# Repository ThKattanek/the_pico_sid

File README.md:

# ThePicoSID
This is a MOS-6581 / MOS-8580 replacement on the base from reSID on the raspberry pi pico or rp2040.
The first pcb prototype, for stable testings.

#### Here are a few videos of me in german language.

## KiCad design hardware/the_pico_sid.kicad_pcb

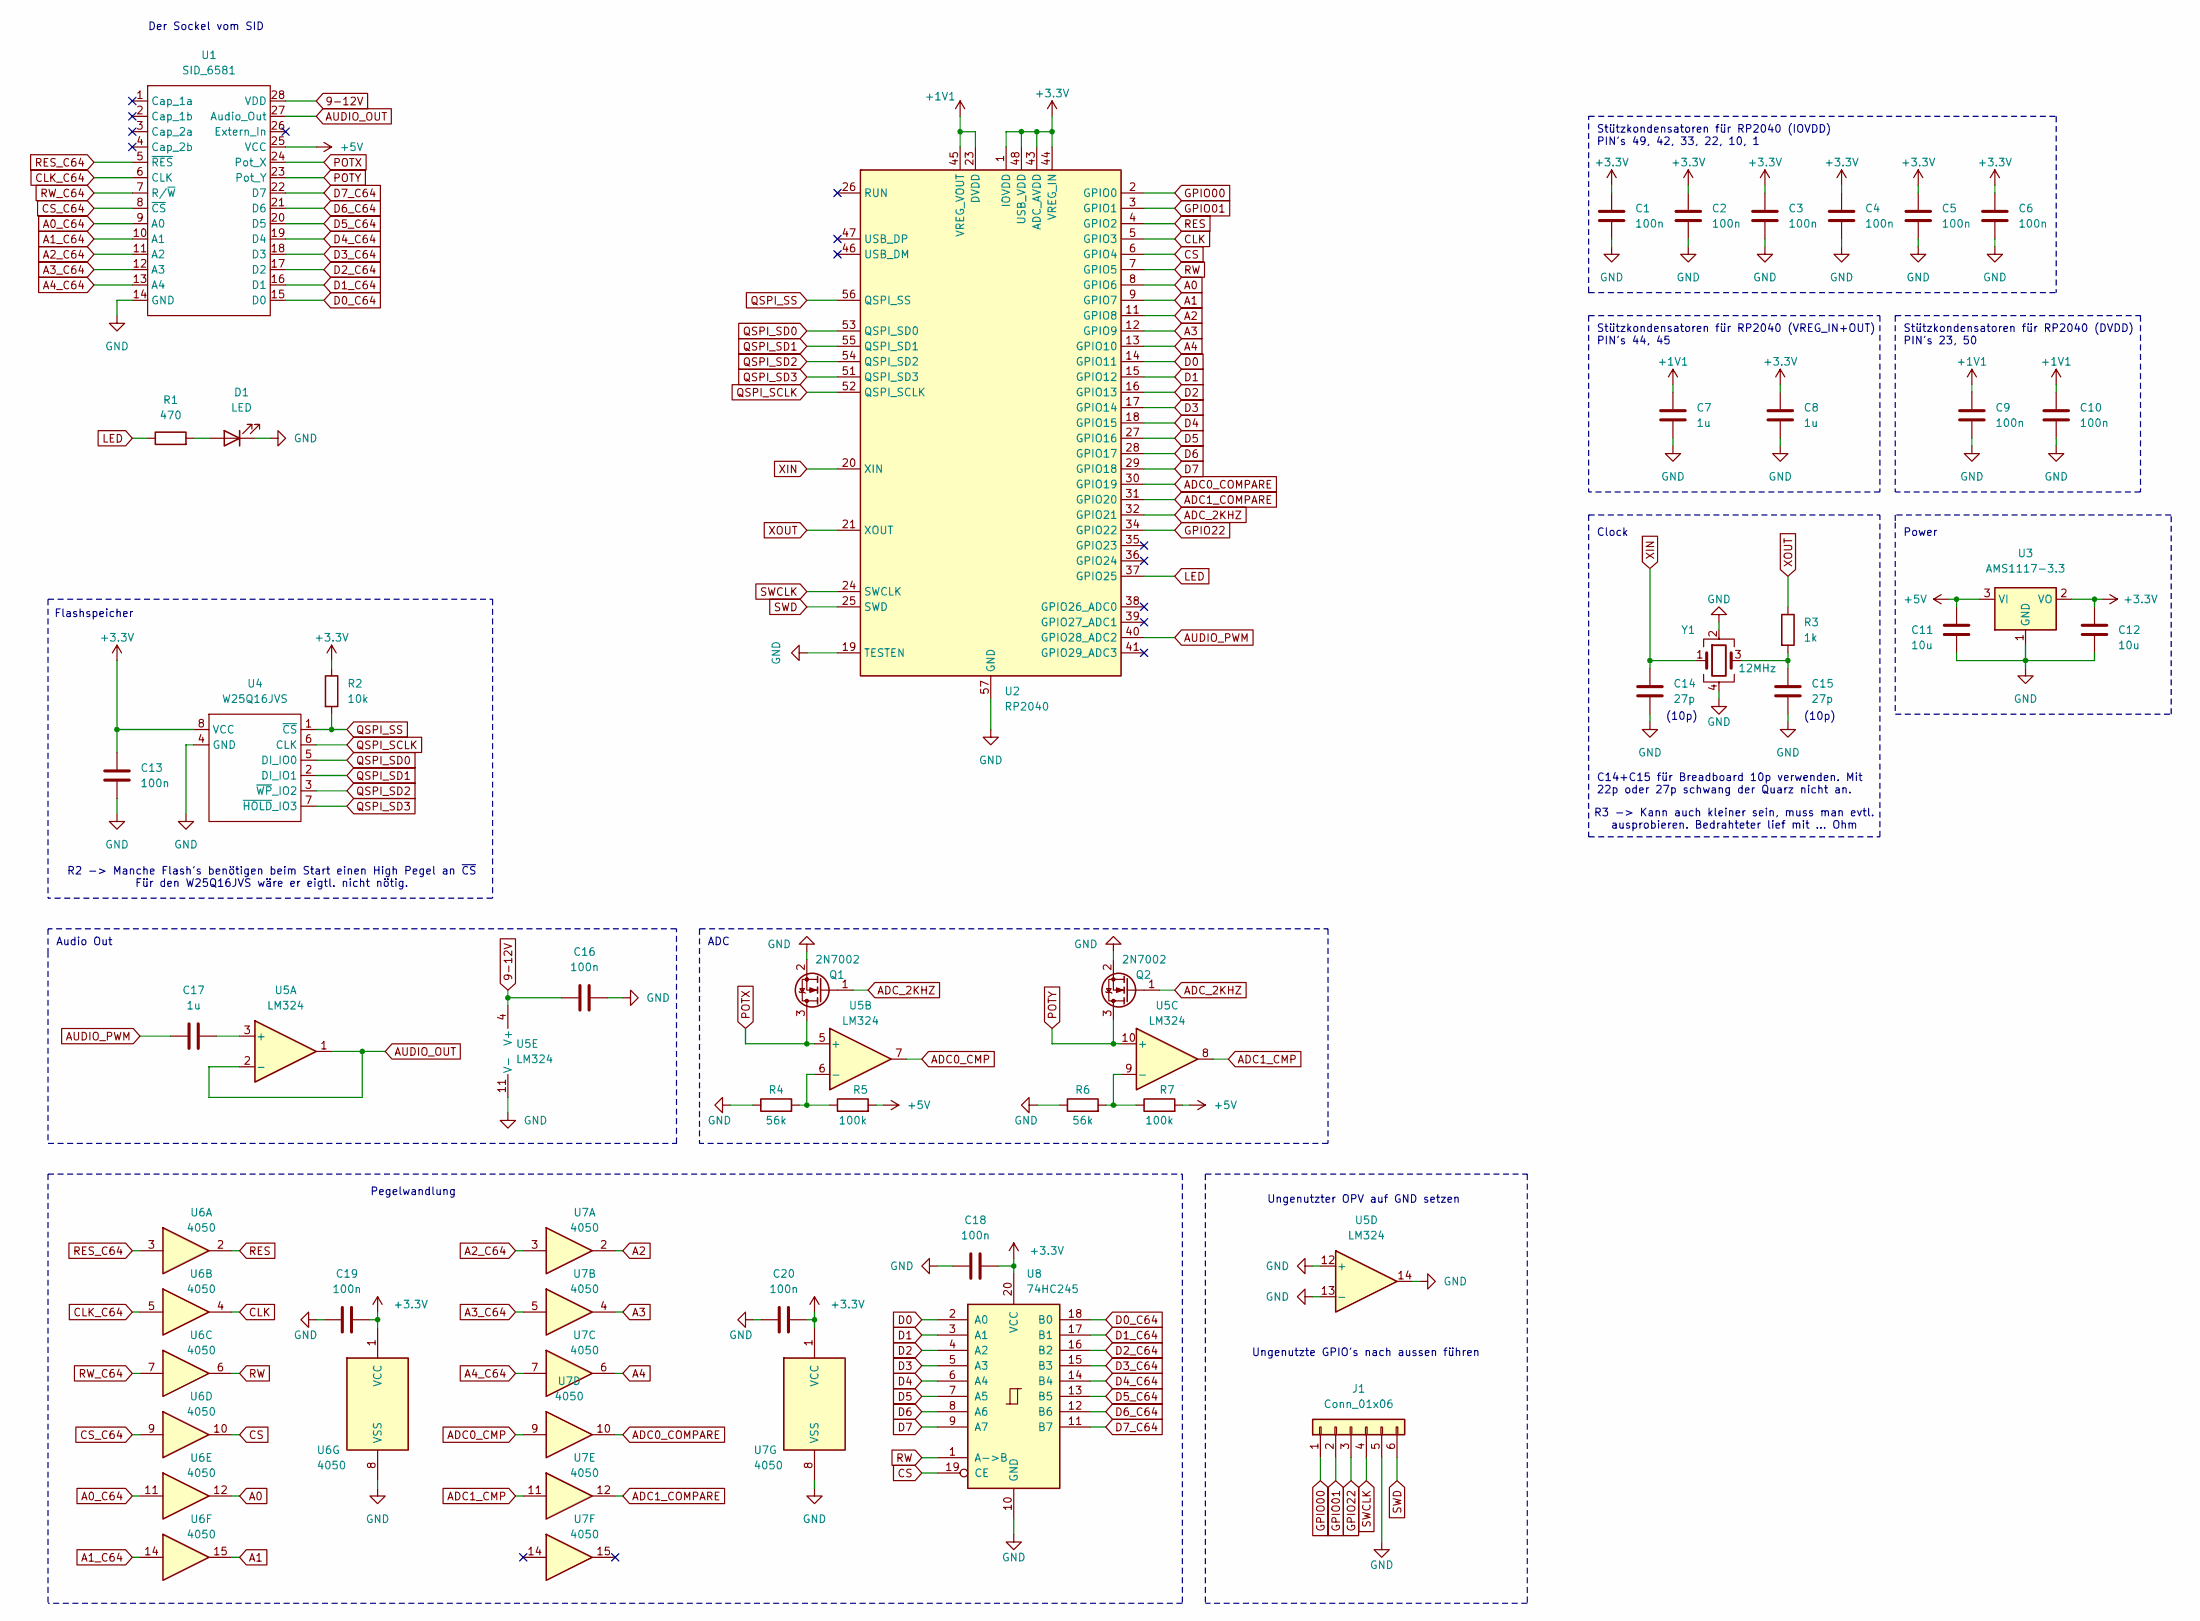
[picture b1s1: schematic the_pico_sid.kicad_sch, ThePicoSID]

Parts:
C1, C2, C3, C4, C5, C6, C9, C10, C13, C16, C18, C19, C20: 100n; C_0603_1608Metric
C7, C8, C17: 1u; C_0603_1608Metric
C11, C12: 10u; C_0603_1608Metric
C14, C15: 27p; C_0603_1608Metric
D1: LED; LED_0805_2012Metric
J1: Conn_01x06; PinSocket_1x06_P1.27mm_Vertical
Q1, Q2: 2N7002; SOT-23
R1: 470; R_0603_1608Metric
R2: 10k; R_0603_1608Metric
R3: 1k; R_0603_1608Metric
R4, R6: 56k; R_0603_1608Metric
R5, R7: 100k; R_0603_1608Metric
U1: SID_6581; c64_sid_pins
U2: RP2040; QFN-56-1EP_7x7mm_P0.4mm_EP3.2x3.2mm
U3: AMS1117-3.3; SOT-223-3_TabPin2
U4: W25Q16JVS; SO-8_5.3x6.2mm_P1.27mm
U5: LM324; SOIC-14_3.9x8.7mm_P1.27mm
U6, U7: 4050; SOIC-16_3.9x9.9mm_P1.27mm
U8: 74HC245; SOIC-20W_7.5x12.8mm_P1.27mm
Y1: 12MHz; Crystal_SMD_EuroQuartz_MJ-4Pin_5.0x3.2mm

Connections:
9-12V: C16.1, U1.28 (VDD), U5.4 (V+)
+1V1: C7.1, C9.1, C10.1, U2.23 (DVDD), U2.45 (VREG_VOUT), U2.50 (DVDD)
+3.3V: C1.1, C2.1, C3.1, C4.1, C5.1, C6.1, C8.1, C12.1, C13.1, C18.2, C19.2, C20.2, R2.1, U2.1 (IOVDD), U2.10 (IOVDD), U2.22 (IOVDD), U2.33 (IOVDD), U2.42 (IOVDD), U2.43 (ADC_AVDD), U2.44 (VREG_IN), U2.48 (USB_VDD), U2.49 (IOVDD), U3.2 (VO), U4.8 (VCC), U6.1 (VCC), U7.1 (VCC), U8.20 (VCC)
+5V: C11.1, R5.2, R7.2, U1.25 (VCC), U3.3 (VI)
A0: U2.8 (GPIO6), U6.12
A0_C64: U1.9 (A0), U6.11
A1: U2.9 (GPIO7), U6.15
A1_C64: U1.10 (A1), U6.14
A2: U2.11 (GPIO8), U7.2
A2_C64: U1.11 (A2), U7.3
A3: U2.12 (GPIO9), U7.4
A3_C64: U1.12 (A3), U7.5
A4: U2.13 (GPIO10), U7.6
A4_C64: U1.13 (A4), U7.7
ADC0_CMP: U5.7, U7.9
ADC0_COMPARE: U2.30 (GPIO19), U7.10
ADC1_CMP: U5.8, U7.11
ADC1_COMPARE: U2.31 (GPIO20), U7.12
ADC_2KHZ: Q1.1 (G), Q2.1 (G), U2.32 (GPIO21)
AUDIO_OUT: U1.27 (Audio_Out), U5.1, U5.2 (-)
AUDIO_PWM: C17.1, U2.40 (GPIO28_ADC2)
CLK: U2.5 (GPIO3), U6.4
CLK_C64: U1.6 (CLK), U6.5
CS: U2.6 (GPIO4), U6.10, U8.19 (CE)
CS_C64: U1.8 (~CS), U6.9
D0: U2.14 (GPIO11), U8.2 (A0)
D0_C64: U1.15 (D0), U8.18 (B0)
D1: U2.15 (GPIO12), U8.3 (A1)
D1_C64: U1.16 (D1), U8.17 (B1)
D2: U2.16 (GPIO13), U8.4 (A2)
D2_C64: U1.17 (D2), U8.16 (B2)
D3: U2.17 (GPIO14), U8.5 (A3)
D3_C64: U1.18 (D3), U8.15 (B3)
D4: U2.18 (GPIO15), U8.6 (A4)
D4_C64: U1.19 (D4), U8.14 (B4)
D5: U2.27 (GPIO16), U8.7 (A5)
D5_C64: U1.20 (D5), U8.13 (B5)
D6: U2.28 (GPIO17), U8.8 (A6)
D6_C64: U1.21 (D6), U8.12 (B6)
D7: U2.29 (GPIO18), U8.9 (A7)
D7_C64: U1.22 (D7), U8.11 (B7)
GND: C1.2, C2.2, C3.2, C4.2, C5.2, C6.2, C7.2, C8.2, C9.2, C10.2, C11.2, C12.2, C13.2, C14.2, C15.2, C16.2, C18.1, C19.1, C20.1, D1.1 (K), J1.5, Q1.2 (S), Q2.2 (S), R4.1, R6.1, U1.14 (GND), U2.19 (TESTEN), U2.57 (GND), U3.1 (GND), U4.4 (GND), U5.11 (V-), U5.12 (+), U5.13 (-), U5.14, U6.8 (VSS), U7.8 (VSS), U8.10 (GND), Y1.2, Y1.4
GPIO00: J1.1, U2.2 (GPIO0)
GPIO01: J1.2, U2.3 (GPIO1)
GPIO22: J1.3, U2.34 (GPIO22)
LED: R1.1, U2.37 (GPIO25)
unnamed: C15.1, R3.2, Y1.3
unnamed: D1.2 (A), R1.2
unnamed: C17.2, U5.3 (+)
unnamed: R4.2, R5.1, U5.6 (-)
unnamed: R6.2, R7.1, U5.9 (-)
POTX: Q1.3 (D), U1.24 (Pot_X), U5.5 (+)
POTY: Q2.3 (D), U1.23 (Pot_Y), U5.10 (+)
QSPI_SCLK: U2.52 (QSPI_SCLK), U4.6 (CLK)
QSPI_SD0: U2.53 (QSPI_SD0), U4.5 (DI_IO0)
QSPI_SD1: U2.55 (QSPI_SD1), U4.2 (DI_IO1)
QSPI_SD2: U2.54 (QSPI_SD2), U4.3 (~WP_IO2)
QSPI_SD3: U2.51 (QSPI_SD3), U4.7 (~HOLD_IO3)
QSPI_SS: R2.2, U2.56 (QSPI_SS), U4.1 (~CS)
RES: U2.4 (GPIO2), U6.2
RES_C64: U1.5 (~RES), U6.3
RW: U2.7 (GPIO5), U6.6, U8.1 (A->B)
RW_C64: U1.7 (R/~W), U6.7
SWCLK: J1.4, U2.24 (SWCLK)
SWD: J1.6, U2.25 (SWD)
XIN: C14.1, U2.20 (XIN), Y1.1
XOUT: R3.1, U2.21 (XOUT)

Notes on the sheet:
Ungenutzter OPV auf GND setzen
Stützkondensatoren für RP2040 (DVDD) PIN's 23, 50
(10p)
Der Sockel vom SID
Clock
Audio Out
Power
Stützkondensatoren für RP2040 (VREG_IN+OUT) PIN's 44, 45
Flashspeicher
R3 -> Kann auch kleiner sein, muss man evtl. ausprobieren. Bedrahteter lief mit ... Ohm
R2 -> Manche Flash's benötigen beim Start einen High Pegel an ~{CS} Für den W25Q16JVS wäre er eigtl. nicht nötig.
Pegelwandlung
Stützkondensatoren für RP2040 (IOVDD) PIN's 49, 42, 33, 22, 10, 1
C14+C15 für Breadboard 10p verwenden. Mit 22p oder 27p schwang der Quarz nicht an.
Ungenutzte GPIO's nach aussen führen
ADC

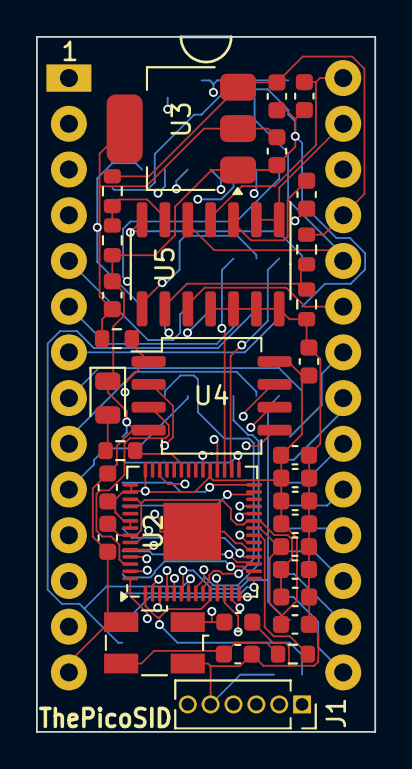
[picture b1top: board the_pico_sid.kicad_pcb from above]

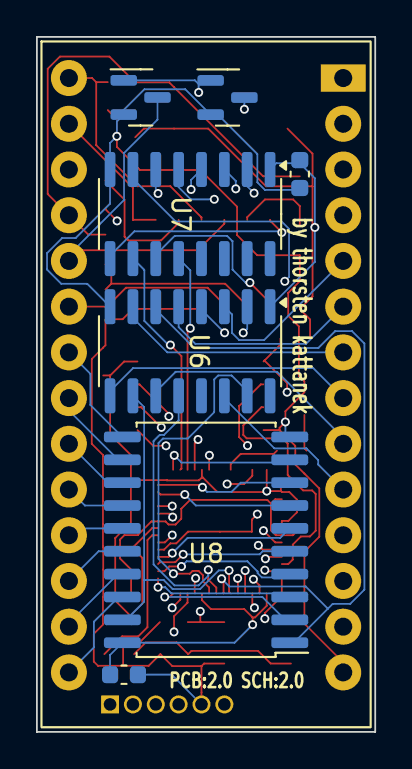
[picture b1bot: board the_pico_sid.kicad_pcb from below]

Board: 4 copper layers, 18.8 x 38.6 mm, 40 parts (8 on the bottom side), 67 nets.

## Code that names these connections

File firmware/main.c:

//////////////////////////////////////////////////
//                                              //
// ThePicoSID                                   //
// von Thorsten Kattanek                        //
//                                              //
// #file: main.c                                //
//                                              //
// https://github.com/ThKattanek/the_pico_sid   //
//                                              //
//////////////////////////////////////////////////

#include <stdio.h>
#include <pico/multicore.h>
#include <hardware/pio.h>
#include <hardware/dma.h>
#include <hardware/pwm.h>
#include <hardware/adc.h>

#include "write_sid_reg.pio.h"
#include "read_sid_reg.pio.h"
#include "dma_read.pio.h"

#include "sid.h"

#include "version.h"

// PIN MAPPING
#define RES_PIN 2
#define CLK_PIN 3		// Atention: When change this gpio, then also change this in write_sid_reg.pio
#define CS_PIN 4
#define RW_PIN 5
#define ADRR_PIN 6
#define DATA_PIN 11
#define AUDIO_PIN 28
#define ADC0_COMPARE_PIN 19
#define ADC1_COMPARE_PIN 20
#define ADC_2KHz_PIN 21

#define PICO_LED_PIN 25

#define ADC_OFFSET -5



volatile bool reset_state = true;

volatile PIO pio;
volatile uint sm0;	// write sid
volatile uint sm1;	// read sid
volatile uint sm2;	// dma read

volatile uint slice_num;

void InitPWMAudio(uint audio_out_gpio);
void DmaReadInit(PIO pio, uint sm, uint8_t* base_address);

void C64Reset(uint gpio, uint32_t events) 
{
    if (events & GPIO_IRQ_EDGE_FALL) 
	{
		// C64 Reset
		// Normalerweise erst wenn RESET 10 Zyklen auf Lo war
        SidSetAudioOut(false);
		SidReset();
    }
	else if (events & GPIO_IRQ_EDGE_RISE) 
	{
		// C64 Reset Ende
        SidSetAudioOut(true);
    }
}

void WriteSidReg()
{
	if (pio0_hw->irq & 1) 
	{
		pio0_hw->irq = 1;

		uint16_t incomming = pio->rxf[sm0];
		SidWriteReg(incomming >> 2, (incomming >> 7) & 0xff);
	}
}

void Core1Entry() 
{
	InitPWMAudio(AUDIO_PIN);

    while (1)
	{
	}
}

void GetVersionNumber(uint8_t *major, uint8_t *minor, uint8_t *patch)
{
	*major = VERSION_MAJOR;
	*minor = VERSION_MINOR;
	*patch = VERSION_PATCH;
}

int main() {

	//default clock is 125000kHz
	set_sys_clock_khz(248000, true); // Kann Normal bis 133MHz laufen, funktioniert bei mir auch bis 266MHz

	stdio_init_all();	

	// Pico LED
	gpio_init(PICO_LED_PIN);
	gpio_set_dir(PICO_LED_PIN, true);
	gpio_put(PICO_LED_PIN, true);

	// ADC
	gpio_init(ADC_2KHz_PIN);
	gpio_set_dir(ADC_2KHz_PIN, true);	// Output

	gpio_init(ADC0_COMPARE_PIN);
	gpio_init(ADC1_COMPARE_PIN);

	gpio_set_dir(ADC0_COMPARE_PIN, false);	// Input
	gpio_set_dir(ADC1_COMPARE_PIN, false);	// Input

	// Init SID
	// memory for the sid io
    uint8_t* sid_io = memalign(32, 32);
	for(int i=0; i<32; i++)
		sid_io[i] = i;

	SidInit(sid_io);
	SidSetChipTyp(MOS_8580);
	SidEnableFilter(true);
	
	// UART Start Message PicoSID
	printf("ThePicoSID by Thorsten Kattanek\n");

	uint8_t v_major, v_minor, v_patch;
	GetVersionNumber(&v_major, &v_minor, &v_patch);

	printf("Firmware Version: %d.%d.%d\n", v_major, v_minor, v_patch);
	
	// PIO Program initialize
	pio = pio0;

	// PIO Write SID
	uint offset = pio_add_program(pio, &write_sid_reg_program);
	sm0 = pio_claim_unused_sm(pio, true);
	write_sid_reg_program_init(pio, sm0, offset, CLK_PIN, CS_PIN);	//CLK_PIN + RW_PIN + A0-A4 + D0-D7 all PIN Count is 15
	irq_set_exclusive_handler(PIO0_IRQ_0, WriteSidReg);
	irq_set_enabled(PIO0_IRQ_0, true);
	pio0_hw->inte0 = PIO_IRQ0_INTE_SM0_BITS;

	// PIO Read SID
	offset = pio_add_program(pio, &read_sid_reg_program);
	sm1 = pio_claim_unused_sm(pio, true);
	read_sid_reg_program_init(pio, sm1, offset, CLK_PIN, CS_PIN, DATA_PIN);

	// PIO DMA READ
	offset = pio_add_program(pio, &dma_read_program);
	sm2 = pio_claim_unused_sm(pio, true);
	dma_read_program_init(pio, sm2, offset, ADRR_PIN, DATA_PIN, sid_io);
	DmaReadInit(pio, sm2, sid_io);

	// IRQ für die RESET Leitung
	gpio_init(RES_PIN);
    gpio_set_dir(RES_PIN, GPIO_IN);
    gpio_set_irq_enabled_with_callback(RES_PIN, GPIO_IRQ_EDGE_RISE | GPIO_IRQ_EDGE_FALL, true, &C64Reset);

	// Start Core#1 for SID Emualtion
	multicore_launch_core1(Core1Entry);

	volatile uint16_t counter;
	volatile bool	adc0_compare_state;
	volatile bool	adc0_compare_state_old;
	volatile bool	adc1_compare_state;
	volatile bool	adc1_compare_state_old;

    while (1)
    {
		// ADC
		sleep_us(1);

		counter++;
		gpio_put(ADC_2KHz_PIN, counter & 0x100);	// Create 2KHz Signal for the mosfet

		// AX
		adc0_compare_state = gpio_get(ADC0_COMPARE_PIN);
		if(adc0_compare_state && !adc0_compare_state_old)
			sid_io[25] = (counter + ADC_OFFSET) & 0xff;
		adc0_compare_state_old = adc0_compare_state;

		// AY
		adc1_compare_state = gpio_get(ADC1_COMPARE_PIN);
		if(adc1_compare_state && !adc1_compare_state_old)
			sid_io[26] = (counter + ADC_OFFSET) & 0xff;
		adc1_compare_state_old = adc1_compare_state;
    }
}

void pwm_irq_handle()
{
	pwm_clear_irq(slice_num);

	for(int i=0; i<6; i++)
	{
		SidCycle(4);
	}

	uint16_t out = ((SidFilterOut() >> 4) + 32768) / (float)0xffff * 0x7ff;
	
	pwm_set_gpio_level(AUDIO_PIN, out);
}

void InitPWMAudio(uint audio_out_gpio)
{
	gpio_set_function(audio_out_gpio, GPIO_FUNC_PWM);
	gpio_set_drive_strength(audio_out_gpio, GPIO_DRIVE_STRENGTH_2MA);

	// Find out which PWM slice is connected to GPIO 2 (it's slice 1)
	slice_num = pwm_gpio_to_slice_num(audio_out_gpio);

	// Set pwm frequenz
	pwm_set_clkdiv_int_frac(slice_num, 2,15);	// PWM Frequency of 41223Hz when Systemclock is 248MHz.

	// Set period of 4 cycles (0 to 3 inclusive)
	pwm_set_wrap(slice_num, 0x07ff);	// 11Bit

	// Set channel A output high for one cycle before dropping
	pwm_set_chan_level(slice_num, PWM_CHAN_A, 0x0400);

	// Set the PWM running
	pwm_set_enabled(slice_num, true);

	// IRQ Swt
	pwm_clear_irq(slice_num);
	pwm_set_irq_enabled(slice_num, true);
	irq_set_exclusive_handler(PWM_IRQ_WRAP, pwm_irq_handle);
	irq_set_enabled(PWM_IRQ_WRAP, true);
}

// Set up DMA channels for handling reads
void DmaReadInit(PIO pio, uint sm, uint8_t* base_address) 
{
    // Read channel: copy requested byte to TX fifo (source address set by write channel below)
    uint read_channel = 0;
    dma_channel_claim(read_channel);

    dma_channel_config read_config = dma_channel_get_default_config(read_channel);
    channel_config_set_read_increment(&read_config, false);
    channel_config_set_write_increment(&read_config, false);
    channel_config_set_dreq(&read_config, pio_get_dreq(pio, sm, true));
    channel_config_set_transfer_data_size(&read_config, DMA_SIZE_8);

    dma_channel_configure(read_channel,
                          &read_config,
                          &pio->txf[sm], // write to TX fifo
                          base_address,  // read from base address (overwritten by write channel)
                          1,             // transfer count
                          false);        // start later

    // Write channel: copy address from RX fifo to the read channel's READ_ADDR_TRIGGER
    uint write_channel = 1;
    dma_channel_claim(write_channel);
    dma_channel_config write_config = dma_channel_get_default_config(write_channel);
    channel_config_set_read_increment(&write_config, false);
    channel_config_set_write_increment(&write_config, false);
    channel_config_set_dreq(&write_config, pio_get_dreq(pio, sm, false));
    channel_config_set_transfer_data_size(&write_config, DMA_SIZE_32);

    volatile void *read_channel_addr = &dma_channel_hw_addr(read_channel)->al3_read_addr_trig;
    dma_channel_configure(write_channel,
                          &write_config,
                          read_channel_addr, // write to read_channel READ_ADDR_TRIGGER
                          &pio->rxf[sm],     // read from RX fifo
                          0xffffffff,        // do many transfers
                          true);             // start now
}

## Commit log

2023-07-25 added the pico project template (blink led)
2023-08-01 added datasheets
2023-08-01 Started schematic with kicad
2023-08-02 added 100n, change pico pins for res, clk, cs, rw
2023-08-02 added audio filter in schematic
2023-08-03 schematic: added five address lines from c64 to pico
2023-08-03 added sid.c and sid.h to firmware
2023-08-03 beginning new docomentation
2023-08-05 schematic: added data lines
2023-08-05 added gpio_mapping.txt
2023-08-06 added first pio assembler program
2023-08-08 change read_sid_reg.pio to write_sid_reg.pio
2023-08-09 firmware: pio statemaschine 1 -> irq when clk=1 and rw=0 and cs=0
2023-08-09 set pico speed of 125mhz
2023-08-12 all voices oscillators implement
2023-08-12 changed audio bitsize from 10 to 11 bits.
2023-08-13 doc: c64 testprogs added
2023-08-13 doc: added problems textfile
2023-08-13 added osc as external files osc.c and osc.h
2023-08-13 firmware: disable ringmod and sync
2023-08-13 firmware: added adsr envelope
2023-08-13 firmware: optimizing osc and env calls
2023-08-13 firmware: change timing
2023-08-16 schematic: add debug_led green or red status
2023-08-16 sheamtic: changed debug led's resitors from 100 to 200 ohm
2023-08-16 firmware: fix pio write_sid_reg
2023-08-16 schematic: led resitors from 200 to 1k ohm
2023-09-08 schematic: added temporary ic 4520 counter
2023-09-08 firmware: used core1 and new clock_2 input
2023-09-10 before emu64 sid implementation
2023-09-13 change .gitignore, added .cache
2023-09-13 firmware: new project structur
2023-09-13 a new qt desktop application platform for the firmware without using Pico and C64
2023-09-13 experiment with 1/8 cycles from c64 clack
2023-09-14 firmware: filter is running / with pico not perfect, in simulation perfekt
2023-09-14 firmware: the filter is now implemented
2023-09-14 desktop_simulation: fixed for better teseting
2023-09-15 firmware: code cleaning
2023-09-16 added siddump from hard and heavy titlescreen
2023-09-16 firmware: added info txt in this files
2023-09-16 schematic: change pin clk with cs, remove counters
2023-09-16 firmware: fixed write_sid_reg.pio
2023-09-16 firmware: cleaning code
2023-09-17 schematic: one 74hc4050 changed to 74hc245 for bidirection data
2023-09-17 firmware: update gpio mapping
2023-09-17 update documentation
2023-09-17 firmware: change write_sid_reg.pio
2023-09-17 doc: added datasheets for tl084 and 74hc245
2023-09-17 doc: added a snippet for a lowpassfilter
2023-09-17 doc: added sid datasheet
2023-09-17 firmware: implement reset handling
2023-09-17 doc: update documentation
2023-09-18 firmware: implement pio programm for read sid and added a callback for this
2023-09-18 firmware: added SidReadReg
2023-10-02 firmware: added dma_read.pio
2023-10-02 firmware: cleaning read_sid_reg.pio
2023-10-02 firmware: cleaning main.c
2023-10-02 firmware: implement read registers 27 and 28
2023-10-03 schematic: added adc
2023-10-03 firmware: added adc
2023-10-03 schematic: change tl084 with lm324. added potx, poty support
2023-10-03 firmware: adc read every 512us
2023-10-03 doc: added pictures from the breadboard prototype
2023-10-07 doc: added a oszi picture
2023-10-07 schematic: changed the adc implementation
2023-10-07 firmware: added new adc
2023-10-07 firmware: added an offset for ADC's
2023-10-07 schematic: replace potentiometers with constant resistors
2023-10-07 doc: rename a picture directory
2023-10-07 doc: added new pictures from the breadboard rev1.2
2023-10-08 shematic: mosfets swap, BS170 -> 2N7002
2023-10-09 schematic: change footprint for 4050 from SO14 to SO16
2023-10-09 doc: added new render pictures from the first prototype
2023-10-09 Hardware: cretated the first pcb
2023-10-21 hardware: added bom for pcb 1.0
2023-10-29 hardware: update bom for pcb 1.0
2023-11-13 firmware: a comment updated
2023-11-13 firmware: update sid_desktop_simulation
2023-11-13 added resid support only for sid_desktop_simulation
2023-11-16 remove resid implementation
2023-11-16 doc: added new commands for thepicosid config
2023-11-16 firmware: added version number
2023-11-16 desktop simulation: added fw version
2023-11-17 firmware: added pico led on
2023-11-18 firmware: change to c++ and remove old sid emulation
2023-11-18 firmware: change pico sid desktop simulation for new class
2023-11-19 only as backup to github #01
2023-11-19 only as backup to github #02
2023-11-22 only as backup to github #03
2023-11-23 only as backup to github #04
2023-11-23 destop_simulation: added three envelope osc views
2023-11-25 firmware: new implement envelope from resid
2023-11-25 only as backup to github #05
2023-11-25 only as backup to github #06
2023-11-26 only as backup to github #07
2023-11-29 firmware: change to 300MHz Sytemclock and used inline
2023-11-29 firmware added filter from resid 1.6
2023-11-29 firmware: audio level higher
2023-11-29 firmware_ switch to 248MHz
2023-12-01 doc: change documantation
2023-12-01 firmware: add read osc3 and env3
2023-12-02 firmware: best audio output
2023-12-02 firmware: added configuration output over the uart
2023-12-02 firmware: added extfilter
2023-12-03 desktop_sim_tool: addes checkboxes for Filter and ExtFilter
2023-12-03 firmware: added fixed samples and digiboost for 8580
2023-12-03 start the c64 config tool
2023-12-05 firmware: added config and read firmware version
2023-12-05 c64_config_tool: added read firmware version and detect thepicosid
2023-12-12 only as backup to github #08
2023-12-16 firmware: fixed version number read
2023-12-16 c64_config_tool: implements menu functions
2023-12-17 c64_config_tool: the menu is final
2023-12-17 c64_config_tool: is final
2023-12-17 firmware: added flash support, is but buggy
2023-12-18 firmware: config writing now in the flash memory
2023-12-23 Update version.h
    Update main.cpp
2023-12-23 rename c64 config tool directory
2023-12-28 added new images
2023-12-28 Update README.md
    added videos from the pico sid
2024-01-25 doc: added oszi pictures potax
2024-01-25 doc: added quick guid
2024-01-25 change schematic: adc's inverted input voltage from 1.2V to 1.7V
2024-02-20 schematic: change from 4050 to resistors for level convertion
2024-02-20 shematic: all footprints added
2024-02-20 schematic: added testpoints for usb and boot_sel
2024-02-20 schematic: added more testpoints
2024-02-20 shematic: added testpoint for 1,1V
2024-02-20 pcb: first position all components in size from a sid
2024-02-24 convert to kicad 8.0
2024-03-17 schematic + pcb update
2024-03-17 new gerber files for pcb 2.0
2024-03-24 pcb: update
2024-03-28 new pcb and gerber files for JLCPCB production
2024-03-28 added a euroquarz model
2024-04-13 Added Notes for the crystal and there capacitors
2024-04-22 firmware: change the system clock from 300MHz to 292MHz
2024-04-23 added pictures
2024-04-29 firmware: changed systemclock for a stable run from 300MHz to 280MHz
2024-04-30 firmware: change the system clock to 279MHz
2025-03-26 build: update CMake configuration and set C++ standard to 17 feat: define SYSTEM_CLOCK for consistent clock settings chore: add .gitignore for build artifacts
2025-03-26 fix: correct comment for SYSTEM_CLOCK in main.cpp to reflect Prototype 2
